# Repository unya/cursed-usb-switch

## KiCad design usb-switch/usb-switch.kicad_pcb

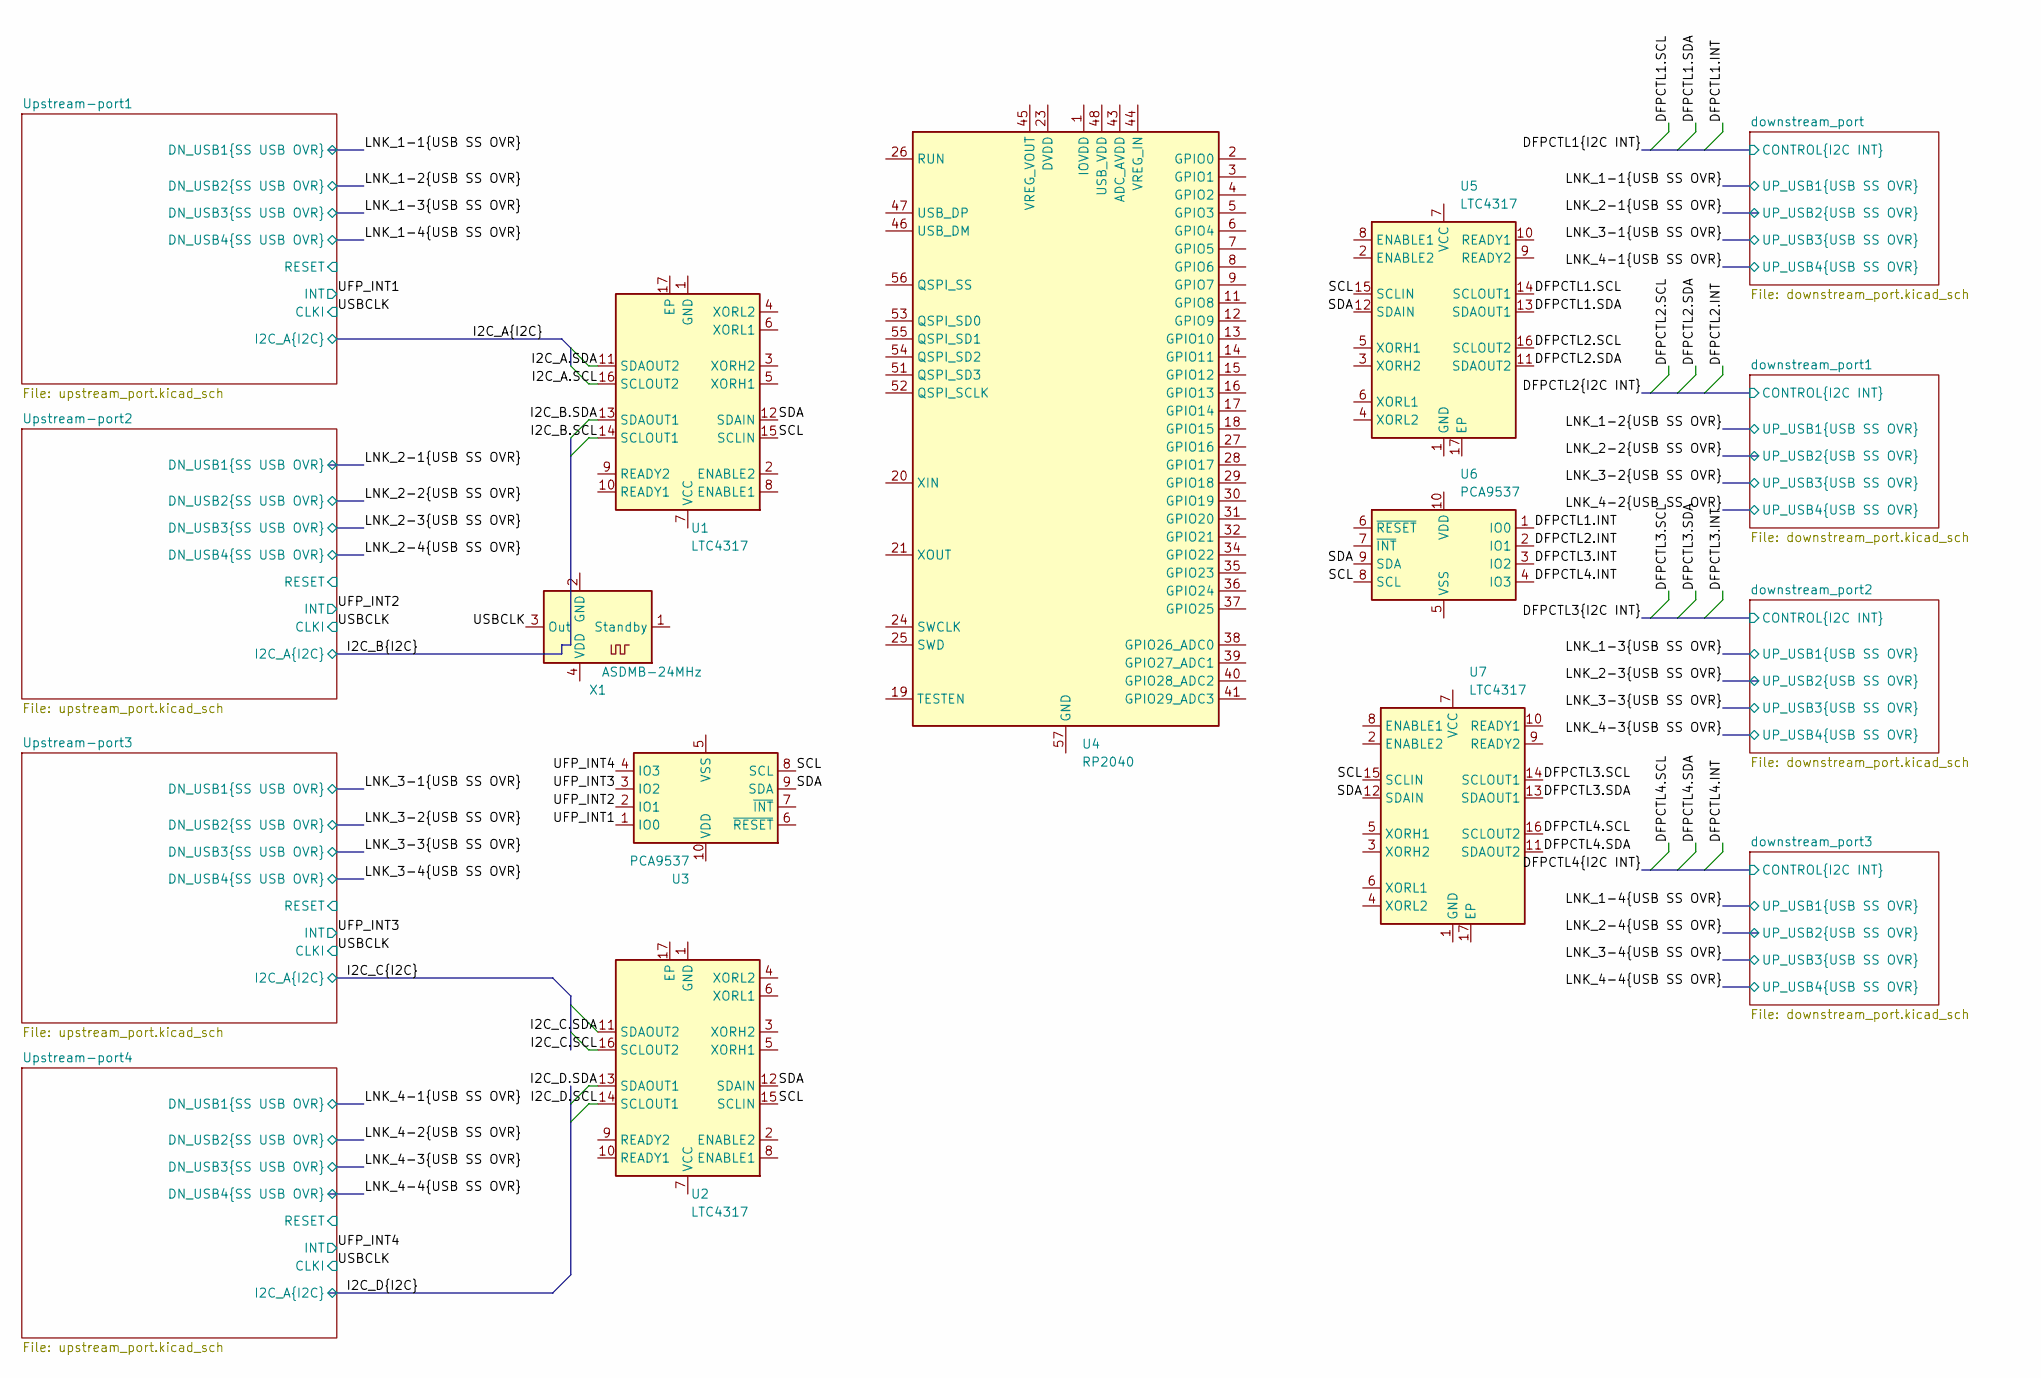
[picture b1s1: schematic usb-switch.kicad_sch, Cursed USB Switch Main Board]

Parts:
U1, U2, U5, U7: LTC4317; DFN-16-1EP_3x5mm_P0.5mm_EP1.66x4.4mm
U3, U6: PCA9537; TSSOP-10_3x3mm_P0.5mm
U4: RP2040; QFN-56-1EP_7x7mm_P0.4mm_EP3.2x3.2mm
X1: ASDMB-24MHz; Oscillator_SMD_Abracon_ASDMB-4Pin_2.5x2.0mm

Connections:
/DFPCTL1.INT: U6.1 (IO0); also elsewhere on the board
/DFPCTL1.SCL: U5.14 (SCLOUT1); also elsewhere on the board
/DFPCTL1.SDA: U5.13 (SDAOUT1); also elsewhere on the board
/DFPCTL2.INT: U6.2 (IO1); also elsewhere on the board
/DFPCTL2.SCL: U5.16 (SCLOUT2); also elsewhere on the board
/DFPCTL2.SDA: U5.11 (SDAOUT2); also elsewhere on the board
/DFPCTL3.INT: U6.3 (IO2); also elsewhere on the board
/DFPCTL3.SCL: U7.14 (SCLOUT1); also elsewhere on the board
/DFPCTL3.SDA: U7.13 (SDAOUT1); also elsewhere on the board
/DFPCTL4.INT: U6.4 (IO3); also elsewhere on the board
/DFPCTL4.SCL: U7.16 (SCLOUT2); also elsewhere on the board
/DFPCTL4.SDA: U7.11 (SDAOUT2); also elsewhere on the board
/I2C_A.SCL: U1.16 (SCLOUT2); also elsewhere on the board
/I2C_A.SDA: U1.11 (SDAOUT2); also elsewhere on the board
/I2C_B.SCL: U1.14 (SCLOUT1); also elsewhere on the board
/I2C_B.SDA: U1.13 (SDAOUT1); also elsewhere on the board
/I2C_C.SCL: U2.16 (SCLOUT2); also elsewhere on the board
/I2C_C.SDA: U2.11 (SDAOUT2); also elsewhere on the board
/I2C_D.SCL: U2.14 (SCLOUT1); also elsewhere on the board
/I2C_D.SDA: U2.13 (SDAOUT1); also elsewhere on the board
/SCL: U1.15 (SCLIN), U2.15 (SCLIN), U3.8 (SCL), U5.15 (SCLIN), U6.8 (SCL), U7.15 (SCLIN)
/SDA: U1.12 (SDAIN), U2.12 (SDAIN), U3.9 (SDA), U5.12 (SDAIN), U6.9 (SDA), U7.12 (SDAIN)
/UFP_INT1: U3.1 (IO0); also elsewhere on the board
/UFP_INT2: U3.2 (IO1); also elsewhere on the board
/UFP_INT3: U3.3 (IO2); also elsewhere on the board
/UFP_INT4: U3.4 (IO3); also elsewhere on the board
/USBCLK: X1.3 (Out); also elsewhere on the board
unnamed: U4.23 (DVDD), U4.50 (DVDD)
unnamed: U4.1 (IOVDD), U4.10 (IOVDD), U4.22 (IOVDD), U4.33 (IOVDD), U4.42 (IOVDD), U4.49 (IOVDD)

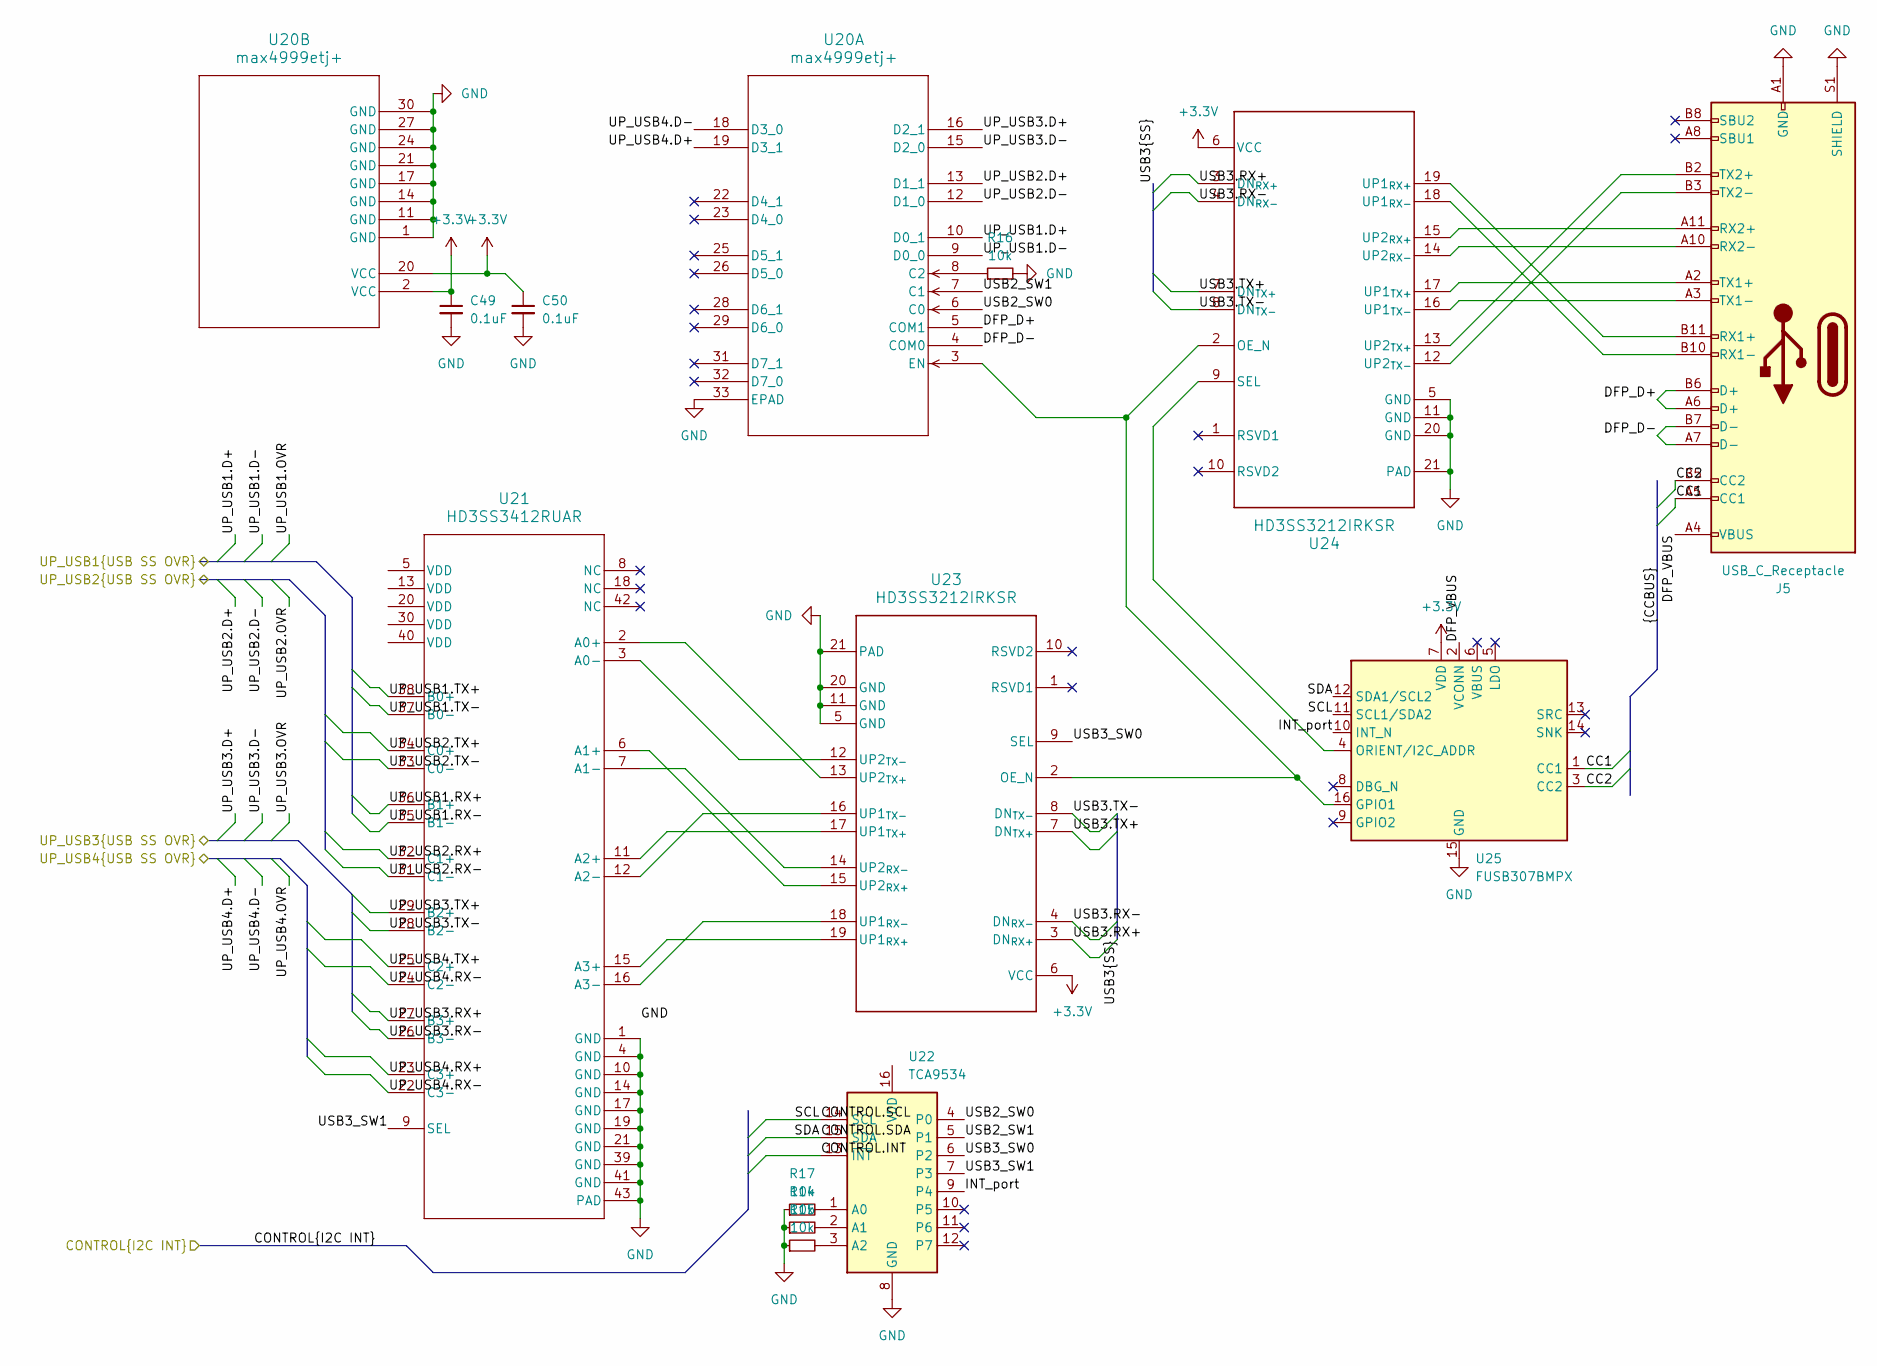
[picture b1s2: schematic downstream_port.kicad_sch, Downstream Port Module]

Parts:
C49, C50: 0.1uF; C_0402_1005Metric
J5: USB_C_Receptacle; USB_C_Receptacle_Amphenol_12401548E4-2A
R14, R15, R16, R17: 10k; R_0201_0603Metric
U20: max4999etj+; 21-0140_T3255+4_MXM
U21: HD3SS3412RUAR; RUA0042A
U22: TCA9534; SOIC-16_4.55x10.3mm_P1.27mm
U23, U24: HD3SS3212IRKSR; RKS0020A
U25: FUSB307BMPX; WQFN-16-1EP_3x3mm_P0.5mm_EP1.75x1.75mm

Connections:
+3.3V: C49.1, C50.1, U20.2 (VCC), U20.20 (VCC), U23.6 (VCC), U24.6 (VCC), U25.7 (VDD); also elsewhere on the board
/DFPCTL1.INT: U22.13 (~INT); also elsewhere on the board
/DFPCTL1.SCL: U22.14 (SCL), U25.11 (SCL1/SDA2); also elsewhere on the board
/DFPCTL1.SDA: U22.15 (SDA), U25.12 (SDA1/SCL2); also elsewhere on the board
/LNK_1-1.D+: U20.10 (D0_1); also elsewhere on the board
/LNK_1-1.D-: U20.9 (D0_0); also elsewhere on the board
/LNK_1-1.RX+: U21.36 (B1+); also elsewhere on the board
/LNK_1-1.RX-: U21.35 (B1-); also elsewhere on the board
/LNK_1-1.TX+: U21.38 (B0+); also elsewhere on the board
/LNK_1-1.TX-: U21.37 (B0-); also elsewhere on the board
/LNK_2-1.D+: U20.13 (D1_1); also elsewhere on the board
/LNK_2-1.D-: U20.12 (D1_0); also elsewhere on the board
/LNK_2-1.RX+: U21.32 (C1+); also elsewhere on the board
/LNK_2-1.RX-: U21.31 (C1-); also elsewhere on the board
/LNK_2-1.TX+: U21.34 (C0+); also elsewhere on the board
/LNK_2-1.TX-: U21.33 (C0-); also elsewhere on the board
/LNK_3-1.D+: U20.16 (D2_1); also elsewhere on the board
/LNK_3-1.D-: U20.15 (D2_0); also elsewhere on the board
/LNK_3-1.RX+: U21.27 (B3+); also elsewhere on the board
/LNK_3-1.RX-: U21.26 (B3-); also elsewhere on the board
/LNK_3-1.TX+: U21.29 (B2+); also elsewhere on the board
/LNK_3-1.TX-: U21.28 (B2-); also elsewhere on the board
/LNK_4-1.D+: U20.19 (D3_1); also elsewhere on the board
/LNK_4-1.D-: U20.18 (D3_0); also elsewhere on the board
/LNK_4-1.RX+: U21.23 (C3+); also elsewhere on the board
/LNK_4-1.RX-: U21.22 (C3-), U21.24 (C2-); also elsewhere on the board
/LNK_4-1.TX+: U21.25 (C2+); also elsewhere on the board
/downstream_port/CC1: J5.A5 (CC1), U25.1 (CC1)
/downstream_port/CC2: J5.B5 (CC2), U25.3 (CC2)
/downstream_port/DFP_D+: J5.A6 (D+), J5.B6 (D+), U20.5 (COM1)
/downstream_port/DFP_D-: J5.A7 (D-), J5.B7 (D-), U20.4 (COM0)
/downstream_port/DFP_VBUS: J5.A4 (VBUS), J5.A9 (VBUS), J5.B4 (VBUS), J5.B9 (VBUS), U25.2 (VCONN)
/downstream_port/INT_port: U22.9 (P4), U25.10 (INT_N)
/downstream_port/USB2_SW0: U20.6 (C0), U22.4 (P0)
/downstream_port/USB2_SW1: U20.7 (C1), U22.5 (P1)
/downstream_port/USB3.RX+: U23.3 (DN_{RX+}), U24.3 (DN_{RX+})
/downstream_port/USB3.RX-: U23.4 (DN_{RX-}), U24.4 (DN_{RX-})
/downstream_port/USB3.TX+: U23.7 (DN_{TX+}), U24.7 (DN_{TX+})
/downstream_port/USB3.TX-: U23.8 (DN_{TX-}), U24.8 (DN_{TX-})
/downstream_port/USB3_SW0: U22.6 (P2), U23.9 (SEL)
/downstream_port/USB3_SW1: U21.9 (SEL), U22.7 (P3)
GND: C49.2, C50.2, J5.A1 (GND), J5.A12 (GND), J5.B1 (GND), J5.B12 (GND), J5.S1 (SHIELD), R14.1, R15.1, R16.2, R17.1, U20.1 (GND), U20.11 (GND), U20.14 (GND), U20.17 (GND), U20.21 (GND), U20.24 (GND), U20.27 (GND), U20.30 (GND), U20.33 (EPAD), U21.1 (GND), U21.4 (GND), U21.10 (GND), U21.14 (GND), U21.17 (GND), U21.19 (GND), U21.21 (GND), U21.39 (GND), U21.41 (GND), U21.43 (PAD), U22.8 (GND), U23.5 (GND), U23.11 (GND), U23.20 (GND), U23.21 (PAD), U24.5 (GND), U24.11 (GND), U24.20 (GND), U24.21 (PAD), U25.15 (GND), U25.17 (GND); also elsewhere on the board
unnamed: J5.B11 (RX1+), U24.19 (UP1_{RX+})
unnamed: J5.B10 (RX1-), U24.18 (UP1_{RX-})
unnamed: J5.A11 (RX2+), U24.15 (UP2_{RX+})
unnamed: J5.A10 (RX2-), U24.14 (UP2_{RX-})
unnamed: J5.A2 (TX1+), U24.17 (UP1_{TX+})
unnamed: J5.A3 (TX1-), U24.16 (UP1_{TX-})
unnamed: J5.B2 (TX2+), U24.13 (UP2_{TX+})
unnamed: J5.B3 (TX2-), U24.12 (UP2_{TX-})
unnamed: R16.1, U20.8 (C2)
unnamed: U20.3 (EN), U23.2 (OE_N), U24.2 (OE_N), U25.16 (GPIO1)
unnamed: U21.2 (A0+), U23.13 (UP2_{TX+})
unnamed: U21.3 (A0-), U23.12 (UP2_{TX-})
unnamed: U21.6 (A1+), U23.15 (UP2_{RX+})
unnamed: U21.7 (A1-), U23.14 (UP2_{RX-})
unnamed: U21.11 (A2+), U23.17 (UP1_{TX+})
unnamed: U21.12 (A2-), U23.16 (UP1_{TX-})
unnamed: U21.15 (A3+), U23.19 (UP1_{RX+})
unnamed: U21.16 (A3-), U23.18 (UP1_{RX-})
unnamed: R14.2, U22.2 (A1)
unnamed: R15.2, U22.3 (A2)
unnamed: U24.9 (SEL), U25.4 (ORIENT/I2C_ADDR)

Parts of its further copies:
C51, C52, C53, C54, C55, C56: 0.1uF; C_0402_1005Metric
J6, J7, J8: USB_C_Receptacle; USB_C_Receptacle_Amphenol_12401548E4-2A
R13, R18, R19, R20, R21, R22, R23, R24, R25, R26, R27, R28: 10k; R_0201_0603Metric
U26, U32, U38: max4999etj+; 21-0140_T3255+4_MXM
U27, U33, U39: HD3SS3412RUAR; RUA0042A
U28, U34, U40: TCA9534; SOIC-16_4.55x10.3mm_P1.27mm
U29, U30, U35, U36, U41, U42: HD3SS3212IRKSR; RKS0020A
U31, U37, U43: FUSB307BMPX; WQFN-16-1EP_3x3mm_P0.5mm_EP1.75x1.75mm

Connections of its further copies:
+3.3V: C51.1, C52.1, C53.1, C54.1, C55.1, C56.1, U26.2 (VCC), U26.20 (VCC), U29.6 (VCC), U30.6 (VCC), U31.7 (VDD), U32.2 (VCC), U32.20 (VCC), U35.6 (VCC), U36.6 (VCC), U37.7 (VDD), U38.2 (VCC), U38.20 (VCC), U41.6 (VCC), U42.6 (VCC), U43.7 (VDD); also elsewhere on the board
/DFPCTL2.INT: U28.13 (~INT); also elsewhere on the board
/DFPCTL2.SCL: U28.14 (SCL), U31.11 (SCL1/SDA2); also elsewhere on the board
/DFPCTL2.SDA: U28.15 (SDA), U31.12 (SDA1/SCL2); also elsewhere on the board
/DFPCTL3.INT: U34.13 (~INT); also elsewhere on the board
/DFPCTL3.SCL: U34.14 (SCL), U37.11 (SCL1/SDA2); also elsewhere on the board
/DFPCTL3.SDA: U34.15 (SDA), U37.12 (SDA1/SCL2); also elsewhere on the board
/DFPCTL4.INT: U40.13 (~INT); also elsewhere on the board
/DFPCTL4.SCL: U40.14 (SCL), U43.11 (SCL1/SDA2); also elsewhere on the board
/DFPCTL4.SDA: U40.15 (SDA), U43.12 (SDA1/SCL2); also elsewhere on the board
/LNK_1-2.D+: U26.10 (D0_1); also elsewhere on the board
/LNK_1-2.D-: U26.9 (D0_0); also elsewhere on the board
/LNK_1-2.RX+: U27.36 (B1+); also elsewhere on the board
/LNK_1-2.RX-: U27.35 (B1-); also elsewhere on the board
/LNK_1-2.TX+: U27.38 (B0+); also elsewhere on the board
/LNK_1-2.TX-: U27.37 (B0-); also elsewhere on the board
/LNK_1-3.D+: U32.10 (D0_1); also elsewhere on the board
/LNK_1-3.D-: U32.9 (D0_0); also elsewhere on the board
/LNK_1-3.RX+: U33.36 (B1+); also elsewhere on the board
/LNK_1-3.RX-: U33.35 (B1-); also elsewhere on the board
/LNK_1-3.TX+: U33.38 (B0+); also elsewhere on the board
/LNK_1-3.TX-: U33.37 (B0-); also elsewhere on the board
/LNK_1-4.D+: U38.10 (D0_1); also elsewhere on the board
/LNK_1-4.D-: U38.9 (D0_0); also elsewhere on the board
/LNK_1-4.RX+: U39.36 (B1+); also elsewhere on the board
/LNK_1-4.RX-: U39.35 (B1-); also elsewhere on the board
/LNK_1-4.TX+: U39.38 (B0+); also elsewhere on the board
/LNK_1-4.TX-: U39.37 (B0-); also elsewhere on the board
/LNK_2-2.D+: U26.13 (D1_1); also elsewhere on the board
/LNK_2-2.D-: U26.12 (D1_0); also elsewhere on the board
/LNK_2-2.RX+: U27.32 (C1+); also elsewhere on the board
/LNK_2-2.RX-: U27.31 (C1-); also elsewhere on the board
/LNK_2-2.TX+: U27.34 (C0+); also elsewhere on the board
/LNK_2-2.TX-: U27.33 (C0-); also elsewhere on the board
/LNK_2-3.D+: U32.13 (D1_1); also elsewhere on the board
/LNK_2-3.D-: U32.12 (D1_0); also elsewhere on the board
/LNK_2-3.RX+: U33.32 (C1+); also elsewhere on the board
/LNK_2-3.RX-: U33.31 (C1-); also elsewhere on the board
/LNK_2-3.TX+: U33.34 (C0+); also elsewhere on the board
/LNK_2-3.TX-: U33.33 (C0-); also elsewhere on the board
/LNK_2-4.D+: U38.13 (D1_1); also elsewhere on the board
/LNK_2-4.D-: U38.12 (D1_0); also elsewhere on the board
/LNK_2-4.RX+: U39.32 (C1+); also elsewhere on the board
/LNK_2-4.RX-: U39.31 (C1-); also elsewhere on the board
/LNK_2-4.TX+: U39.34 (C0+); also elsewhere on the board
/LNK_2-4.TX-: U39.33 (C0-); also elsewhere on the board
/LNK_3-2.D+: U26.16 (D2_1); also elsewhere on the board
/LNK_3-2.D-: U26.15 (D2_0); also elsewhere on the board
/LNK_3-2.RX+: U27.27 (B3+); also elsewhere on the board
/LNK_3-2.RX-: U27.26 (B3-); also elsewhere on the board
/LNK_3-2.TX+: U27.29 (B2+); also elsewhere on the board
/LNK_3-2.TX-: U27.28 (B2-); also elsewhere on the board
/LNK_3-3.D+: U32.16 (D2_1); also elsewhere on the board
/LNK_3-3.D-: U32.15 (D2_0); also elsewhere on the board
/LNK_3-3.RX+: U33.27 (B3+); also elsewhere on the board
/LNK_3-3.RX-: U33.26 (B3-); also elsewhere on the board
/LNK_3-3.TX+: U33.29 (B2+); also elsewhere on the board
/LNK_3-3.TX-: U33.28 (B2-); also elsewhere on the board
/LNK_3-4.D+: U38.16 (D2_1); also elsewhere on the board
/LNK_3-4.D-: U38.15 (D2_0); also elsewhere on the board
/LNK_3-4.RX+: U39.27 (B3+); also elsewhere on the board
/LNK_3-4.RX-: U39.26 (B3-); also elsewhere on the board
/LNK_3-4.TX+: U39.29 (B2+); also elsewhere on the board
/LNK_3-4.TX-: U39.28 (B2-); also elsewhere on the board
/LNK_4-2.D+: U26.19 (D3_1); also elsewhere on the board
/LNK_4-2.D-: U26.18 (D3_0); also elsewhere on the board
/LNK_4-2.RX+: U27.23 (C3+); also elsewhere on the board
/LNK_4-2.RX-: U27.22 (C3-), U27.24 (C2-); also elsewhere on the board
/LNK_4-2.TX+: U27.25 (C2+); also elsewhere on the board
/LNK_4-3.D+: U32.19 (D3_1); also elsewhere on the board
/LNK_4-3.D-: U32.18 (D3_0); also elsewhere on the board
/LNK_4-3.RX+: U33.23 (C3+); also elsewhere on the board
/LNK_4-3.RX-: U33.22 (C3-), U33.24 (C2-); also elsewhere on the board
/LNK_4-3.TX+: U33.25 (C2+); also elsewhere on the board
/LNK_4-4.D+: U38.19 (D3_1); also elsewhere on the board
/LNK_4-4.D-: U38.18 (D3_0); also elsewhere on the board
/LNK_4-4.RX+: U39.23 (C3+); also elsewhere on the board
/LNK_4-4.RX-: U39.22 (C3-), U39.24 (C2-); also elsewhere on the board
/LNK_4-4.TX+: U39.25 (C2+); also elsewhere on the board
/downstream_port1/CC1: J6.A5 (CC1), U31.1 (CC1)
/downstream_port1/CC2: J6.B5 (CC2), U31.3 (CC2)
/downstream_port1/DFP_D+: J6.A6 (D+), J6.B6 (D+), U26.5 (COM1)
/downstream_port1/DFP_D-: J6.A7 (D-), J6.B7 (D-), U26.4 (COM0)
/downstream_port1/DFP_VBUS: J6.A4 (VBUS), J6.A9 (VBUS), J6.B4 (VBUS), J6.B9 (VBUS), U31.2 (VCONN)
/downstream_port1/INT_port: U28.9 (P4), U31.10 (INT_N)
/downstream_port1/USB2_SW0: U26.6 (C0), U28.4 (P0)
/downstream_port1/USB2_SW1: U26.7 (C1), U28.5 (P1)
/downstream_port1/USB3.RX+: U29.3 (DN_{RX+}), U30.3 (DN_{RX+})
/downstream_port1/USB3.RX-: U29.4 (DN_{RX-}), U30.4 (DN_{RX-})
/downstream_port1/USB3.TX+: U29.7 (DN_{TX+}), U30.7 (DN_{TX+})
/downstream_port1/USB3.TX-: U29.8 (DN_{TX-}), U30.8 (DN_{TX-})
/downstream_port1/USB3_SW0: U28.6 (P2), U29.9 (SEL)
/downstream_port1/USB3_SW1: U27.9 (SEL), U28.7 (P3)
/downstream_port2/CC1: J7.A5 (CC1), U37.1 (CC1)
/downstream_port2/CC2: J7.B5 (CC2), U37.3 (CC2)
/downstream_port2/DFP_D+: J7.A6 (D+), J7.B6 (D+), U32.5 (COM1)
/downstream_port2/DFP_D-: J7.A7 (D-), J7.B7 (D-), U32.4 (COM0)
/downstream_port2/DFP_VBUS: J7.A4 (VBUS), J7.A9 (VBUS), J7.B4 (VBUS), J7.B9 (VBUS), U37.2 (VCONN)
/downstream_port2/INT_port: U34.9 (P4), U37.10 (INT_N)
/downstream_port2/USB2_SW0: U32.6 (C0), U34.4 (P0)
/downstream_port2/USB2_SW1: U32.7 (C1), U34.5 (P1)
/downstream_port2/USB3.RX+: U35.3 (DN_{RX+}), U36.3 (DN_{RX+})
/downstream_port2/USB3.RX-: U35.4 (DN_{RX-}), U36.4 (DN_{RX-})
/downstream_port2/USB3.TX+: U35.7 (DN_{TX+}), U36.7 (DN_{TX+})
/downstream_port2/USB3.TX-: U35.8 (DN_{TX-}), U36.8 (DN_{TX-})
/downstream_port2/USB3_SW0: U34.6 (P2), U35.9 (SEL)
/downstream_port2/USB3_SW1: U33.9 (SEL), U34.7 (P3)
/downstream_port3/CC1: J8.A5 (CC1), U43.1 (CC1)
/downstream_port3/CC2: J8.B5 (CC2), U43.3 (CC2)
/downstream_port3/DFP_D+: J8.A6 (D+), J8.B6 (D+), U38.5 (COM1)
/downstream_port3/DFP_D-: J8.A7 (D-), J8.B7 (D-), U38.4 (COM0)
/downstream_port3/DFP_VBUS: J8.A4 (VBUS), J8.A9 (VBUS), J8.B4 (VBUS), J8.B9 (VBUS), U43.2 (VCONN)
/downstream_port3/INT_port: U40.9 (P4), U43.10 (INT_N)
/downstream_port3/USB2_SW0: U38.6 (C0), U40.4 (P0)
/downstream_port3/USB2_SW1: U38.7 (C1), U40.5 (P1)
/downstream_port3/USB3.RX+: U41.3 (DN_{RX+}), U42.3 (DN_{RX+})
/downstream_port3/USB3.RX-: U41.4 (DN_{RX-}), U42.4 (DN_{RX-})
/downstream_port3/USB3.TX+: U41.7 (DN_{TX+}), U42.7 (DN_{TX+})
/downstream_port3/USB3.TX-: U41.8 (DN_{TX-}), U42.8 (DN_{TX-})
/downstream_port3/USB3_SW0: U40.6 (P2), U41.9 (SEL)
/downstream_port3/USB3_SW1: U39.9 (SEL), U40.7 (P3)
GND: C51.2, C52.2, C53.2, C54.2, C55.2, C56.2, J6.A1 (GND), J6.A12 (GND), J6.B1 (GND), J6.B12 (GND), J6.S1 (SHIELD), J7.A1 (GND), J7.A12 (GND), J7.B1 (GND), J7.B12 (GND), J7.S1 (SHIELD), J8.A1 (GND), J8.A12 (GND), J8.B1 (GND), J8.B12 (GND), J8.S1 (SHIELD), R13.1, R18.1, R19.1, R20.2, R21.1, R22.1, R23.1, R24.2, R25.1, R26.1, R27.1, R28.2, U26.1 (GND), U26.11 (GND), U26.14 (GND), U26.17 (GND), U26.21 (GND), U26.24 (GND), U26.27 (GND), U26.30 (GND), U26.33 (EPAD), U27.1 (GND), U27.4 (GND), U27.10 (GND), U27.14 (GND), U27.17 (GND), U27.19 (GND), U27.21 (GND), U27.39 (GND), U27.41 (GND), U27.43 (PAD), U28.8 (GND), U29.5 (GND), U29.11 (GND), U29.20 (GND), U29.21 (PAD), U30.5 (GND), U30.11 (GND), U30.20 (GND), U30.21 (PAD), U31.15 (GND), U31.17 (GND), U32.1 (GND), U32.11 (GND), U32.14 (GND), U32.17 (GND), U32.21 (GND), U32.24 (GND), U32.27 (GND), U32.30 (GND), U32.33 (EPAD), U33.1 (GND), U33.4 (GND), U33.10 (GND), U33.14 (GND), U33.17 (GND), U33.19 (GND), U33.21 (GND), U33.39 (GND), U33.41 (GND), U33.43 (PAD), U34.8 (GND), U35.5 (GND), U35.11 (GND), U35.20 (GND), U35.21 (PAD), U36.5 (GND), U36.11 (GND), U36.20 (GND), U36.21 (PAD), U37.15 (GND), U37.17 (GND), U38.1 (GND), U38.11 (GND), U38.14 (GND), U38.17 (GND), U38.21 (GND), U38.24 (GND), U38.27 (GND), U38.30 (GND), U38.33 (EPAD), U39.1 (GND), U39.4 (GND), U39.10 (GND), U39.14 (GND), U39.17 (GND), U39.19 (GND), U39.21 (GND), U39.39 (GND), U39.41 (GND), U39.43 (PAD), U40.8 (GND), U41.5 (GND), U41.11 (GND), U41.20 (GND), U41.21 (PAD), U42.5 (GND), U42.11 (GND), U42.20 (GND), U42.21 (PAD), U43.15 (GND), U43.17 (GND); also elsewhere on the board
unnamed: J6.B11 (RX1+), U30.19 (UP1_{RX+})
unnamed: J6.B10 (RX1-), U30.18 (UP1_{RX-})
unnamed: J6.A11 (RX2+), U30.15 (UP2_{RX+})
unnamed: J6.A10 (RX2-), U30.14 (UP2_{RX-})
unnamed: J6.A2 (TX1+), U30.17 (UP1_{TX+})
unnamed: J6.A3 (TX1-), U30.16 (UP1_{TX-})
unnamed: J6.B2 (TX2+), U30.13 (UP2_{TX+})
unnamed: J6.B3 (TX2-), U30.12 (UP2_{TX-})
unnamed: J7.B11 (RX1+), U36.19 (UP1_{RX+})
unnamed: J7.B10 (RX1-), U36.18 (UP1_{RX-})
unnamed: J7.A11 (RX2+), U36.15 (UP2_{RX+})
unnamed: J7.A10 (RX2-), U36.14 (UP2_{RX-})
unnamed: J7.A2 (TX1+), U36.17 (UP1_{TX+})
unnamed: J7.A3 (TX1-), U36.16 (UP1_{TX-})
unnamed: J7.B2 (TX2+), U36.13 (UP2_{TX+})
unnamed: J7.B3 (TX2-), U36.12 (UP2_{TX-})
unnamed: J8.B11 (RX1+), U42.19 (UP1_{RX+})
unnamed: J8.B10 (RX1-), U42.18 (UP1_{RX-})
unnamed: J8.A11 (RX2+), U42.15 (UP2_{RX+})
unnamed: J8.A10 (RX2-), U42.14 (UP2_{RX-})
unnamed: J8.A2 (TX1+), U42.17 (UP1_{TX+})
unnamed: J8.A3 (TX1-), U42.16 (UP1_{TX-})
unnamed: J8.B2 (TX2+), U42.13 (UP2_{TX+})
unnamed: J8.B3 (TX2-), U42.12 (UP2_{TX-})
unnamed: R20.1, U26.8 (C2)
unnamed: U26.3 (EN), U29.2 (OE_N), U30.2 (OE_N), U31.16 (GPIO1)
unnamed: U27.2 (A0+), U29.13 (UP2_{TX+})
unnamed: U27.3 (A0-), U29.12 (UP2_{TX-})
unnamed: U27.6 (A1+), U29.15 (UP2_{RX+})
unnamed: U27.7 (A1-), U29.14 (UP2_{RX-})
unnamed: U27.11 (A2+), U29.17 (UP1_{TX+})
unnamed: U27.12 (A2-), U29.16 (UP1_{TX-})
unnamed: U27.15 (A3+), U29.19 (UP1_{RX+})
unnamed: U27.16 (A3-), U29.18 (UP1_{RX-})
unnamed: R18.2, U28.2 (A1)
unnamed: R19.2, U28.3 (A2)
unnamed: U30.9 (SEL), U31.4 (ORIENT/I2C_ADDR)
unnamed: R24.1, U32.8 (C2)
unnamed: U32.3 (EN), U35.2 (OE_N), U36.2 (OE_N), U37.16 (GPIO1)
unnamed: U33.2 (A0+), U35.13 (UP2_{TX+})
unnamed: U33.3 (A0-), U35.12 (UP2_{TX-})
unnamed: U33.6 (A1+), U35.15 (UP2_{RX+})
unnamed: U33.7 (A1-), U35.14 (UP2_{RX-})
unnamed: U33.11 (A2+), U35.17 (UP1_{TX+})
unnamed: U33.12 (A2-), U35.16 (UP1_{TX-})
unnamed: U33.15 (A3+), U35.19 (UP1_{RX+})
unnamed: U33.16 (A3-), U35.18 (UP1_{RX-})
unnamed: R21.2, U34.1 (A0)
unnamed: R22.2, U34.2 (A1)
unnamed: R23.2, U34.3 (A2)
unnamed: U36.9 (SEL), U37.4 (ORIENT/I2C_ADDR)
unnamed: R28.1, U38.8 (C2)
unnamed: U38.3 (EN), U41.2 (OE_N), U42.2 (OE_N), U43.16 (GPIO1)
unnamed: U39.2 (A0+), U41.13 (UP2_{TX+})
unnamed: U39.3 (A0-), U41.12 (UP2_{TX-})
unnamed: U39.6 (A1+), U41.15 (UP2_{RX+})
unnamed: U39.7 (A1-), U41.14 (UP2_{RX-})
unnamed: U39.11 (A2+), U41.17 (UP1_{TX+})
unnamed: U39.12 (A2-), U41.16 (UP1_{TX-})
unnamed: U39.15 (A3+), U41.19 (UP1_{RX+})
unnamed: U39.16 (A3-), U41.18 (UP1_{RX-})
unnamed: R25.2, U40.1 (A0)
unnamed: R26.2, U40.2 (A1)
unnamed: R27.2, U40.3 (A2)
unnamed: U42.9 (SEL), U43.4 (ORIENT/I2C_ADDR)
